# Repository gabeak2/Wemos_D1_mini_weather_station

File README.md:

# Wemos_D1_mini_weather_station
Mini weather station built around ESP8266 WiFi SOC on a Wemos D1-Mini breakout PCB.  Shows inside temperature and wifi-updated outside temp, and has LED to indicate for rain.

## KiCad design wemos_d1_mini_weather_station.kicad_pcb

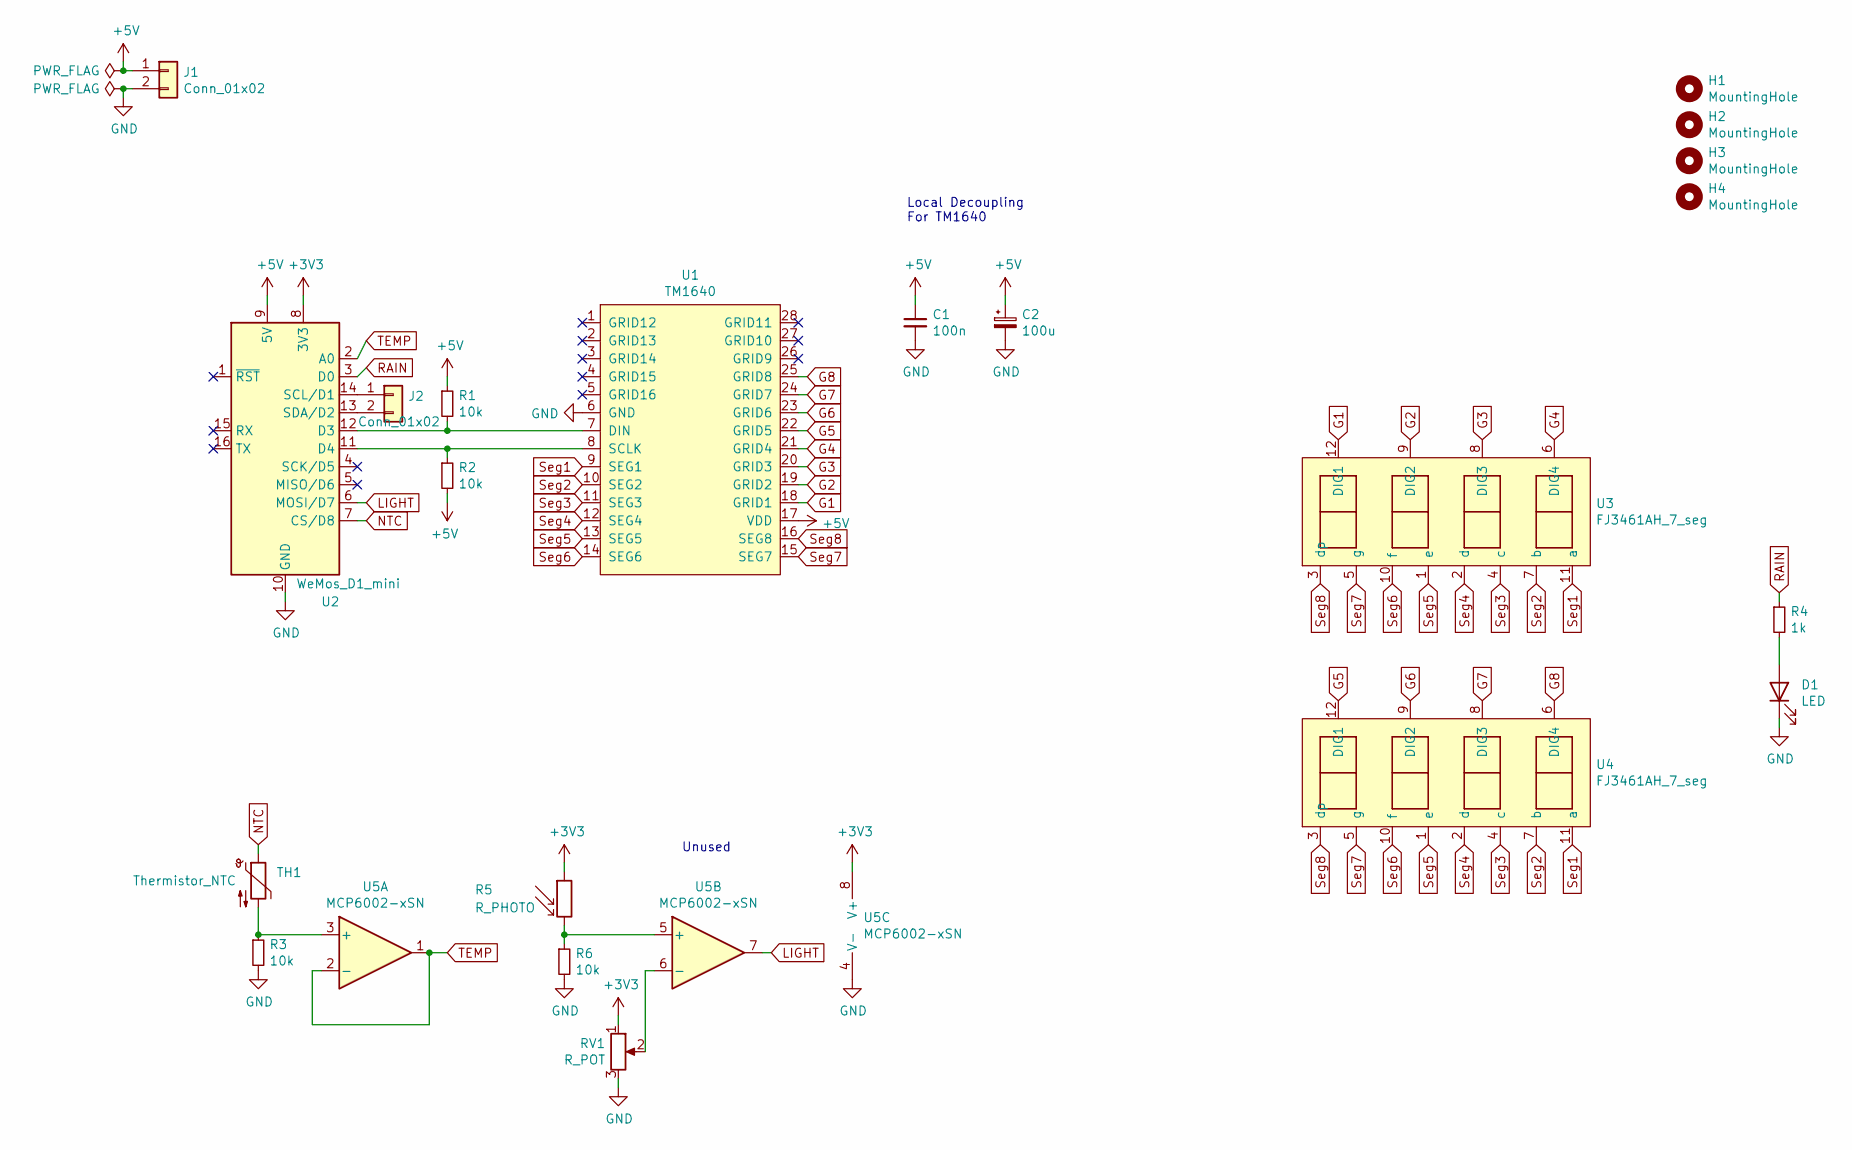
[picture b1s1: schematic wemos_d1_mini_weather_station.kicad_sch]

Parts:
C1: 100n; C_0805_2012Metric
C2: 100u; CP_EIA-7343-31_Kemet-D
D1: LED; LED_D5.0mm
H1, H2, H3, H4: MountingHole; MountingHole_3.2mm_M3
J1, J2: Conn_01x02; PinSocket_1x02_P2.54mm_Vertical
R1, R2, R3, R6: 10k; R_0805_2012Metric
R4: 1k; R_0805_2012Metric
R5: R_PHOTO; PinSocket_1x02_P2.54mm_Vertical
RV1: R_POT; Potentiometer_Bourns_3266Y_Vertical
TH1: Thermistor_NTC; PinSocket_1x02_P2.54mm_Vertical
U1: TM1640; SOIC-28W_7.5x17.9mm_P1.27mm
U2: WeMos_D1_mini; WEMOS_D1_mini_light
U3, U4: FJ3461AH_7_seg; FJ3461AH
U5: MCP6002-xSN; SOIC-8_3.9x4.9mm_P1.27mm

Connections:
+3V3: R5.1, RV1.1, U2.8 (3V3), U5.8 (V+)
+5V: C1.1, C2.1, J1.1, R1.1, R2.2, U1.17 (VDD), U2.9 (5V); also elsewhere on the board
G1: U1.18 (GRID1), U3.12 (DIG1)
G2: U1.19 (GRID2), U3.9 (DIG2)
G3: U1.20 (GRID3), U3.8 (DIG3)
G4: U1.21 (GRID4), U3.6 (DIG4)
G5: U1.22 (GRID5), U4.12 (DIG1)
G6: U1.23 (GRID6), U4.9 (DIG2)
G7: U1.24 (GRID7), U4.8 (DIG3)
G8: U1.25 (GRID8), U4.6 (DIG4)
GND: C1.2, C2.2, D1.1 (K), J1.2, R3.2, R6.2, RV1.3, U1.6 (GND), U2.10 (GND), U5.4 (V-); also elsewhere on the board
LIGHT: U2.6 (MOSI/D7), U5.7
NTC: TH1.1, U2.7 (CS/D8)
unnamed: D1.2 (A), R4.2
unnamed 14: J2.1, U2.14 (SCL/D1); also elsewhere on the board
unnamed 15: J2.2, U2.13 (SDA/D2); also elsewhere on the board
unnamed: R1.2, U1.7 (DIN), U2.12 (D3)
unnamed: R2.1, U1.8 (SCLK), U2.11 (D4)
unnamed: R3.1, TH1.2, U5.3 (+)
unnamed: R5.2, R6.1, U5.5 (+)
unnamed: RV1.2, U5.6 (-)
RAIN: R4.1, U2.3 (D0)
Seg1: U1.9 (SEG1), U3.11 (a), U4.11 (a)
Seg2: U1.10 (SEG2), U3.7 (b), U4.7 (b)
Seg3: U1.11 (SEG3), U3.4 (c), U4.4 (c)
Seg4: U1.12 (SEG4), U3.2 (d), U4.2 (d)
Seg5: U1.13 (SEG5), U3.1 (e), U4.1 (e)
Seg6: U1.14 (SEG6), U3.10 (f), U4.10 (f)
Seg7: U1.15 (SEG7), U3.5 (g), U4.5 (g)
Seg8: U1.16 (SEG8), U3.3 (dp), U4.3 (dp)
TEMP: U2.2 (A0), U5.1, U5.2 (-)

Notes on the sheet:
Local Decoupling For TM1640
Unused

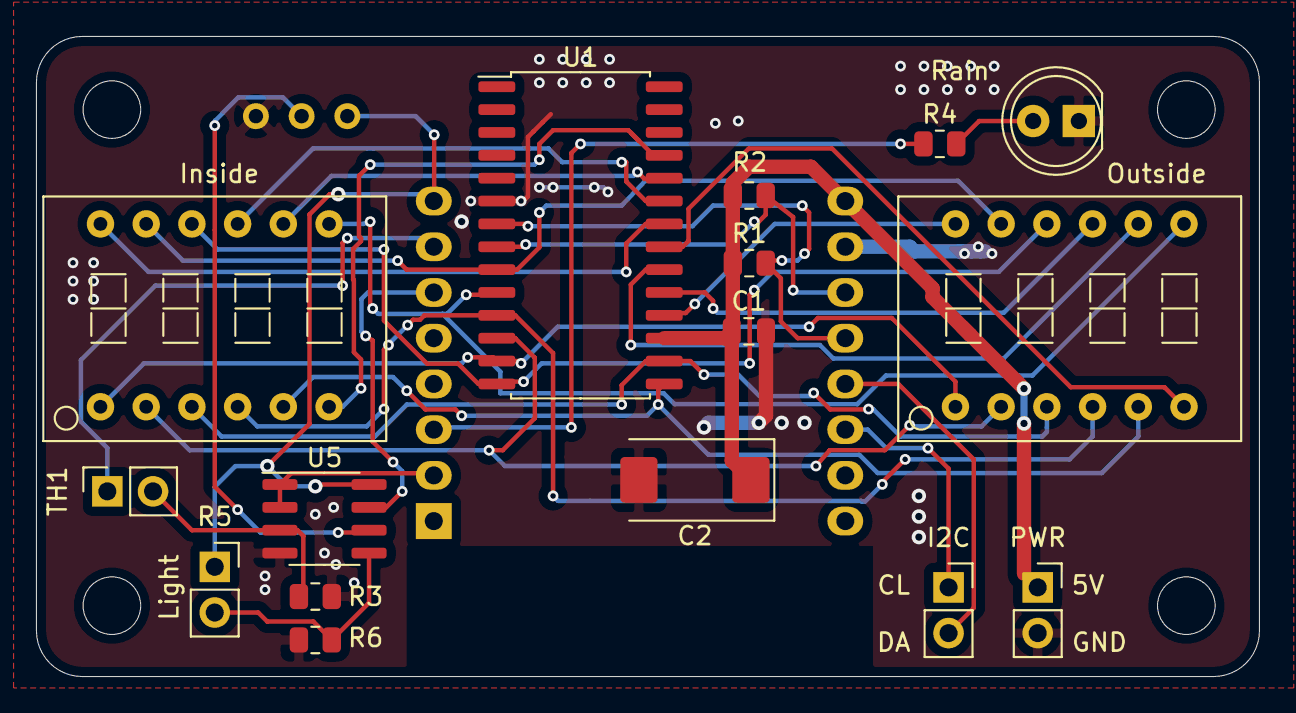
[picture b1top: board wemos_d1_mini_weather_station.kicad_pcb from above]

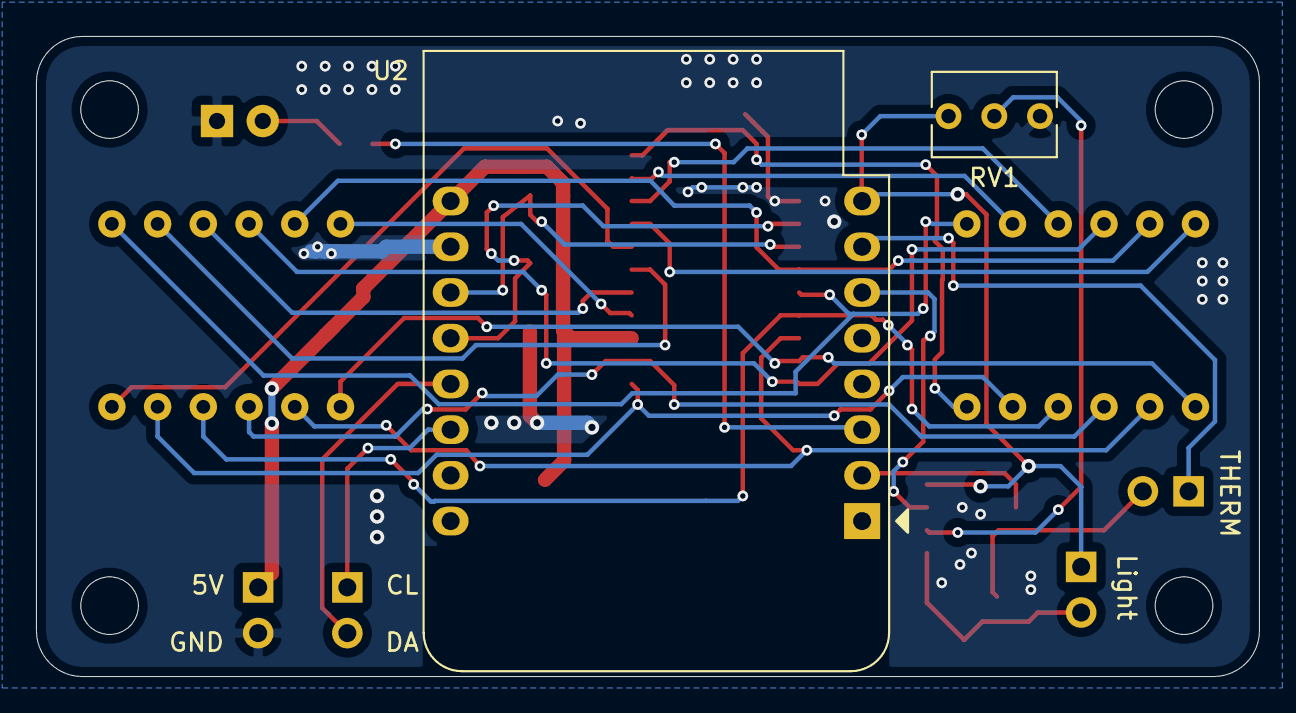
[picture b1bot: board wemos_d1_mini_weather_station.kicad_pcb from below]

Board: 2 copper layers, 67.9 x 35.6 mm, 22 parts (2 on the bottom side), 31 nets.

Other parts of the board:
I2C: Conn_01x02; PinSocket_1x02_P2.54mm_Vertical
PWR: Conn_01x02; PinSocket_1x02_P2.54mm_Vertical

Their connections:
+5V: PWR.1; also elsewhere on the board
GND: PWR.2; also elsewhere on the board
unnamed 14: I2C.1; also elsewhere on the board
unnamed 15: I2C.2; also elsewhere on the board
